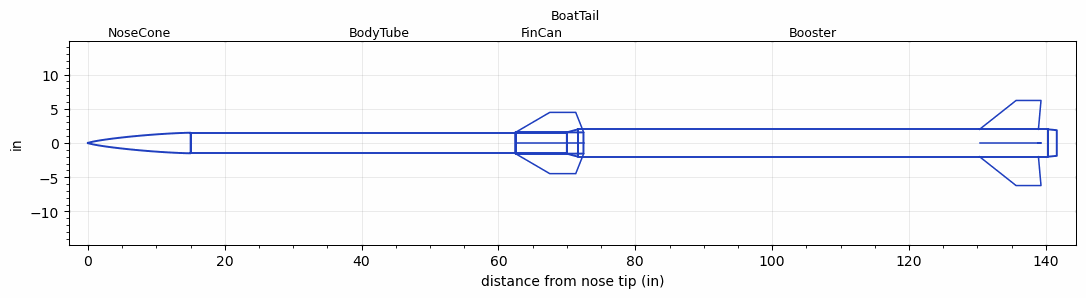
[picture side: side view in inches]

<RASAeroDocument>
 <FileVersion>2</FileVersion>
 <RocketDesign>
  <NoseCone>
   <Length>15</Length>
   <Diameter>3</Diameter>
   <Shape>Von Karman Ogive</Shape>
   <Location>0</Location>
  </NoseCone>
  <BodyTube>
   <Length>55</Length>
   <Diameter>3</Diameter>
   <Location>15</Location>
  </BodyTube>
  <FinCan>
   <Length>7.5</Length>
   <Diameter>3.12</Diameter>
   <InsideDiameter>3</InsideDiameter>
   <Location>70</Location>
   <ShoulderLength>0.0001</ShoulderLength>
   <Offset>-7.5</Offset>
   <Fin>
    <Count>4</Count>
    <Chord>9.948</Chord>
    <Span>2.916</Span>
    <SweepDistance>4.993</SweepDistance>
    <TipChord>3.799</TipChord>
    <Thickness>0.1875</Thickness>
    <LERadius>0.05</LERadius>
    <Location>7.5</Location>
    <AirfoilSection>Hexagonal Blunt Base</AirfoilSection>
    <FX1>0.69</FX1>
    <FX3>0.81</FX3>
   </Fin>
  </FinCan>
  <BoatTail>
   <Length>2.42</Length>
   <Diameter>3.12</Diameter>
   <RearDiameter>3.1</RearDiameter>
   <Location>70</Location>
  </BoatTail>
  <Booster>
   <Length>68.71</Length>
   <Diameter>4</Diameter>
   <InsideDiameter>3.12</InsideDiameter>
   <Location>70</Location>
   <ShoulderLength>1.6122</ShoulderLength>
   <BoattailLength>1.2842</BoattailLength>
   <BoattailRearDiameter>3.75</BoattailRearDiameter>
   <Fin>
    <Count>4</Count>
    <Chord>8.603</Chord>
    <Span>4.219</Span>
    <SweepDistance>5.337</SweepDistance>
    <TipChord>3.641</TipChord>
    <Thickness>0.1875</Thickness>
    <LERadius>0.05</LERadius>
    <Location>10</Location>
    <AirfoilSection>Hexagonal Blunt Base</AirfoilSection>
    <FX1>0.69</FX1>
    <FX3>0.81</FX3>
   </Fin>
  </Booster>
  <Surface>Rough Camouflage Paint</Surface>
  <ModifiedBarrowman>True</ModifiedBarrowman>
  <Turbulence>False</Turbulence>
  <UseBooster1>False</UseBooster1>
  <UseBooster2>False</UseBooster2>
 </RocketDesign>
 <LaunchSite>
  <Altitude>2500</Altitude>
  <Pressure>0</Pressure>
  <RodAngle>0</RodAngle>
  <RodLength>20</RodLength>
  <Temperature>60</Temperature>
  <WindSpeed>5</WindSpeed>
 </LaunchSite>
 <Recovery>
  <Altitude1>1000</Altitude1>
  <Altitude2>1000</Altitude2>
  <DeviceType1>None</DeviceType1>
  <DeviceType2>None</DeviceType2>
  <Event1>False</Event1>
  <Event2>False</Event2>
  <Size1>1</Size1>
  <Size2>1</Size2>
  <EventType1>None</EventType1>
  <EventType2>None</EventType2>
  <CD1>1.33</CD1>
  <CD2>1.33</CD2>
 </Recovery>
 <SimulationList>
  <Simulation>
   <SustainerEngine>M2052  (MIT-SUS)</SustainerEngine>
   <SustainerLaunchWt>23.8</SustainerLaunchWt>
   <SustainerNozzleDiameter>3</SustainerNozzleDiameter>
   <SustainerCG>55.56</SustainerCG>
   <SustainerIgnitionDelay>6</SustainerIgnitionDelay>
   <Booster1Engine>N3787  (MIT-BOOST)</Booster1Engine>
   <Booster1LaunchWt>60.5</Booster1LaunchWt>
   <Booster1SeparationDelay>0</Booster1SeparationDelay>
   <Booster1IgnitionDelay>0</Booster1IgnitionDelay>
   <Booster1CG>97.08</Booster1CG>
   <Booster1NozzleDiameter>3</Booster1NozzleDiameter>
   <IncludeBooster1>True</IncludeBooster1>
   <Booster2Delay>0</Booster2Delay>
   <IncludeBooster2>False</IncludeBooster2>
   <TimetoApogee>26.34043</TimetoApogee>
   <MaxAltitude>11386.66</MaxAltitude>
   <MaxVelocity>940.6477</MaxVelocity>
  </Simulation>
 </SimulationList>
</RASAeroDocument>
